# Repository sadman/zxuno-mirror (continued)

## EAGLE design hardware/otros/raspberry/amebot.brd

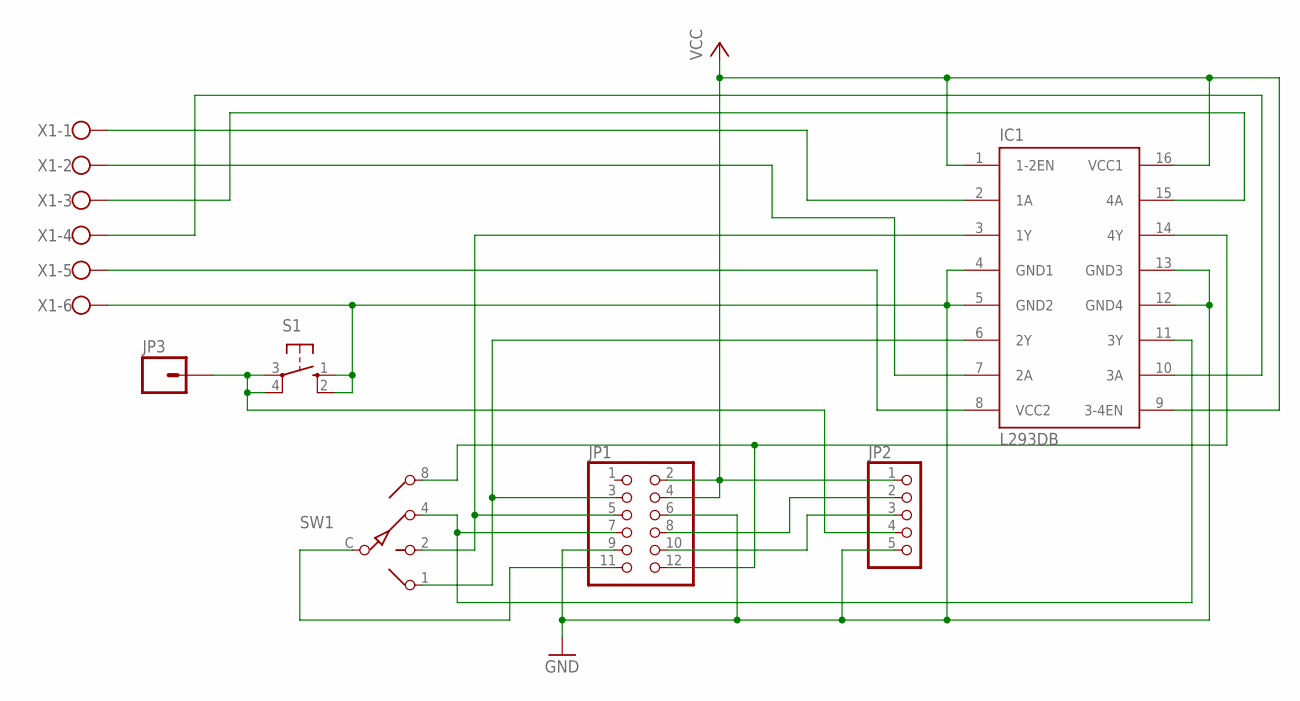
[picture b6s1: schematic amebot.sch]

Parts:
IC1: L293DB; DIL16VAR
JP1: PINHD-2X6; 2X06
JP2: PINHD-1X5; 1X05
JP3: M01PTH_LONGPAD; 1X01_LONGPAD
S1: 10-XX; B3F-10XX
SW1: SW-C10
X1: W237-6

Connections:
GND: IC1.4 (GND1), IC1.5 (GND2), IC1.12 (GND4), IC1.13 (GND3), JP1.6, JP1.9, JP2.5, S1.1 (S), S1.2 (S1), X1.6
unnamed: JP2.4, JP3.1, S1.3, S1.4 (P1)
unnamed: IC1.6 (2Y), JP1.3, SW1.1
unnamed: IC1.3 (1Y), JP1.5, SW1.2
unnamed: JP1.11, SW1.C
unnamed: IC1.14 (4Y), JP1.12, SW1.8
unnamed: JP1.8, JP2.2
unnamed: IC1.2 (1A), X1.1
unnamed: IC1.7 (2A), X1.2
unnamed: IC1.15 (4A), X1.3
unnamed: IC1.10 (3A), X1.4
unnamed: IC1.8 (VCC2), X1.5
unnamed: JP1.10, JP2.3
unnamed: IC1.11 (3Y), JP1.7, SW1.4
VCC: IC1.1 (1-2EN), IC1.9 (3-4EN), IC1.16 (VCC1), JP1.2, JP1.4, JP2.1

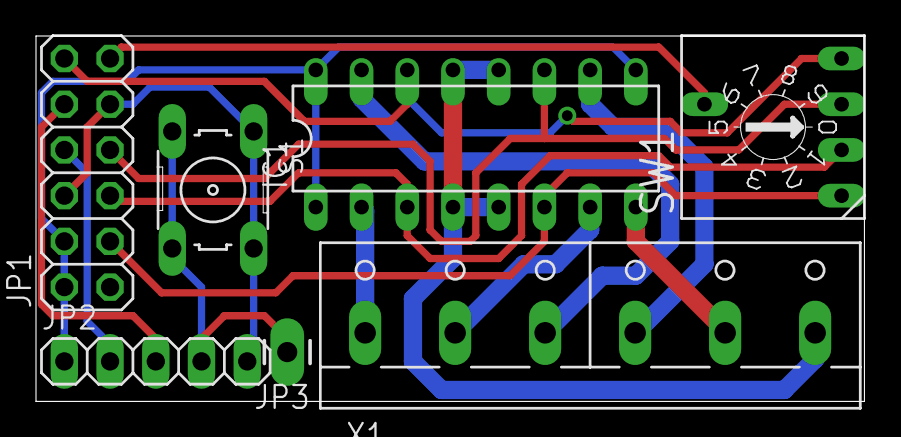
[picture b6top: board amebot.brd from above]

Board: 2 copper layers, 46.0 x 20.3 mm, 7 parts (0 on the bottom side), 15 nets.

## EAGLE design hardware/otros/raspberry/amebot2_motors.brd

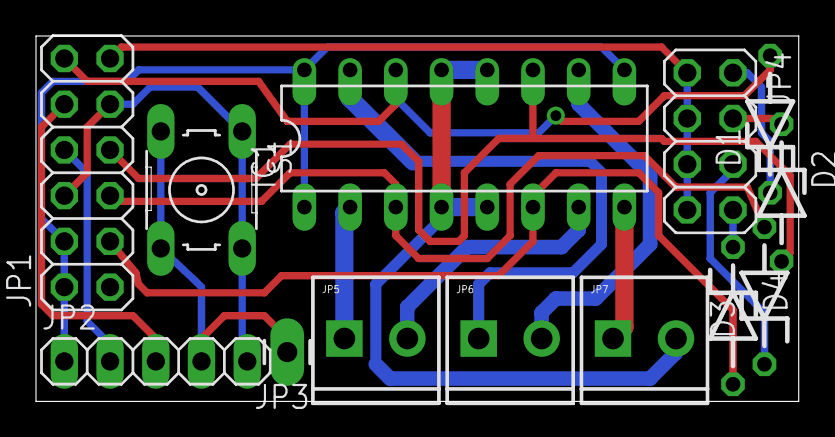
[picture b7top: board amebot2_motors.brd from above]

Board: 2 copper layers, 42.4 x 20.3 mm, 13 parts (0 on the bottom side), 19 nets.

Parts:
D1, D2, D3, D4: ZDIO-7.5
IC1: L293DB; DIL16VAR
JP1: 2X06
JP2: 1X05
JP3: 1X01_LONGPAD
JP4: 2X04
JP5, JP6, JP7: M023.5MM; SCREWTERMINAL-3.5MM-2
S1: B3F-10XX

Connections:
GND: IC1.4, IC1.5, IC1.12, IC1.13, JP1.6, JP1.9, JP2.5, JP7.2, S1.1, S1.2
unnamed: D1.C, JP4.2
unnamed: JP2.4, JP3.1, S1.3, S1.4
unnamed: D4.A, IC1.6, JP1.3
unnamed: D3.A, IC1.3, JP1.5
unnamed: JP1.11, JP4.1, JP4.3, JP4.5, JP4.7
unnamed: D1.A, IC1.14, JP1.12
unnamed: JP1.8, JP2.2
unnamed: IC1.2, JP5.1
unnamed: IC1.7, JP5.2
unnamed: IC1.15, JP6.1
unnamed: IC1.10, JP6.2
unnamed: IC1.8, JP7.1
unnamed: JP1.10, JP2.3
unnamed: D2.A, IC1.11, JP1.7
unnamed: D2.C, JP4.4
unnamed: D3.C, JP4.6
unnamed: D4.C, JP4.8
VCC: IC1.1, IC1.9, IC1.16, JP1.2, JP1.4, JP2.1
